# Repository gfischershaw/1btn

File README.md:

# [1btn](http://www.1btn.space)

1btn (one button) uses the internet to complete a task with the simple, satisfying click of a single button. It connects to the internet over Wi-Fi to trigger whatever action you have assigned to it using a simple, online interface. One click, one task. It’s that simple.

Unlike many other “Internet of Things” devices, 1btn does not maintain a continuous connection to the internet. Instead, it sleeps until it is pressed, then it connects to the internet, performs the assigned task, tells you the outcome via its multi-colored LEDs, and then returns to rest.

As the Internet of Things has expanded, we’ve noticed an unfortunate trend: the increasing use of smartphones to control IoT applications. We don’t think a smartphone provides the best or simplest UI for this purpose. Think of all the steps you need to take to send a single instruction with a smartphone: find the phone, wake it up or power it up, enter your passcode, keep swiping until you find and start up your smart app, select the appropriate control, activate it, and then put the phone back to sleep.

We think there’s a better way, a tried-and-true, more intuitive way, to activate a single task or function, and that’s with a button. Why are buttons such a great idea? A button is the simplest user interface for a single-repetitive-programmable task. They are simple exactly because they are designed for a single-task. More importantly, buttons are easy-to-understand, they are familiar, intuitive, and provide immediate, satisfying physical feedback when pushed.

**Specifications**
- Size: about 60mm diameter
- Casing: hexagonal 3D printed using PLA material
- Built-in rechargeable battery: 3.7V 500mAH
- Built-in wifi module: ESP8266 - ESP-12F
- Weight: approx. 50 grams
- Color: white case bottom with multiple color options for the top (red, pink, blue, yellow, white, and green)

## License
See the [LICENSE] (https://github.com/anandtamboli/1btn/blob/master/LICENSE) file

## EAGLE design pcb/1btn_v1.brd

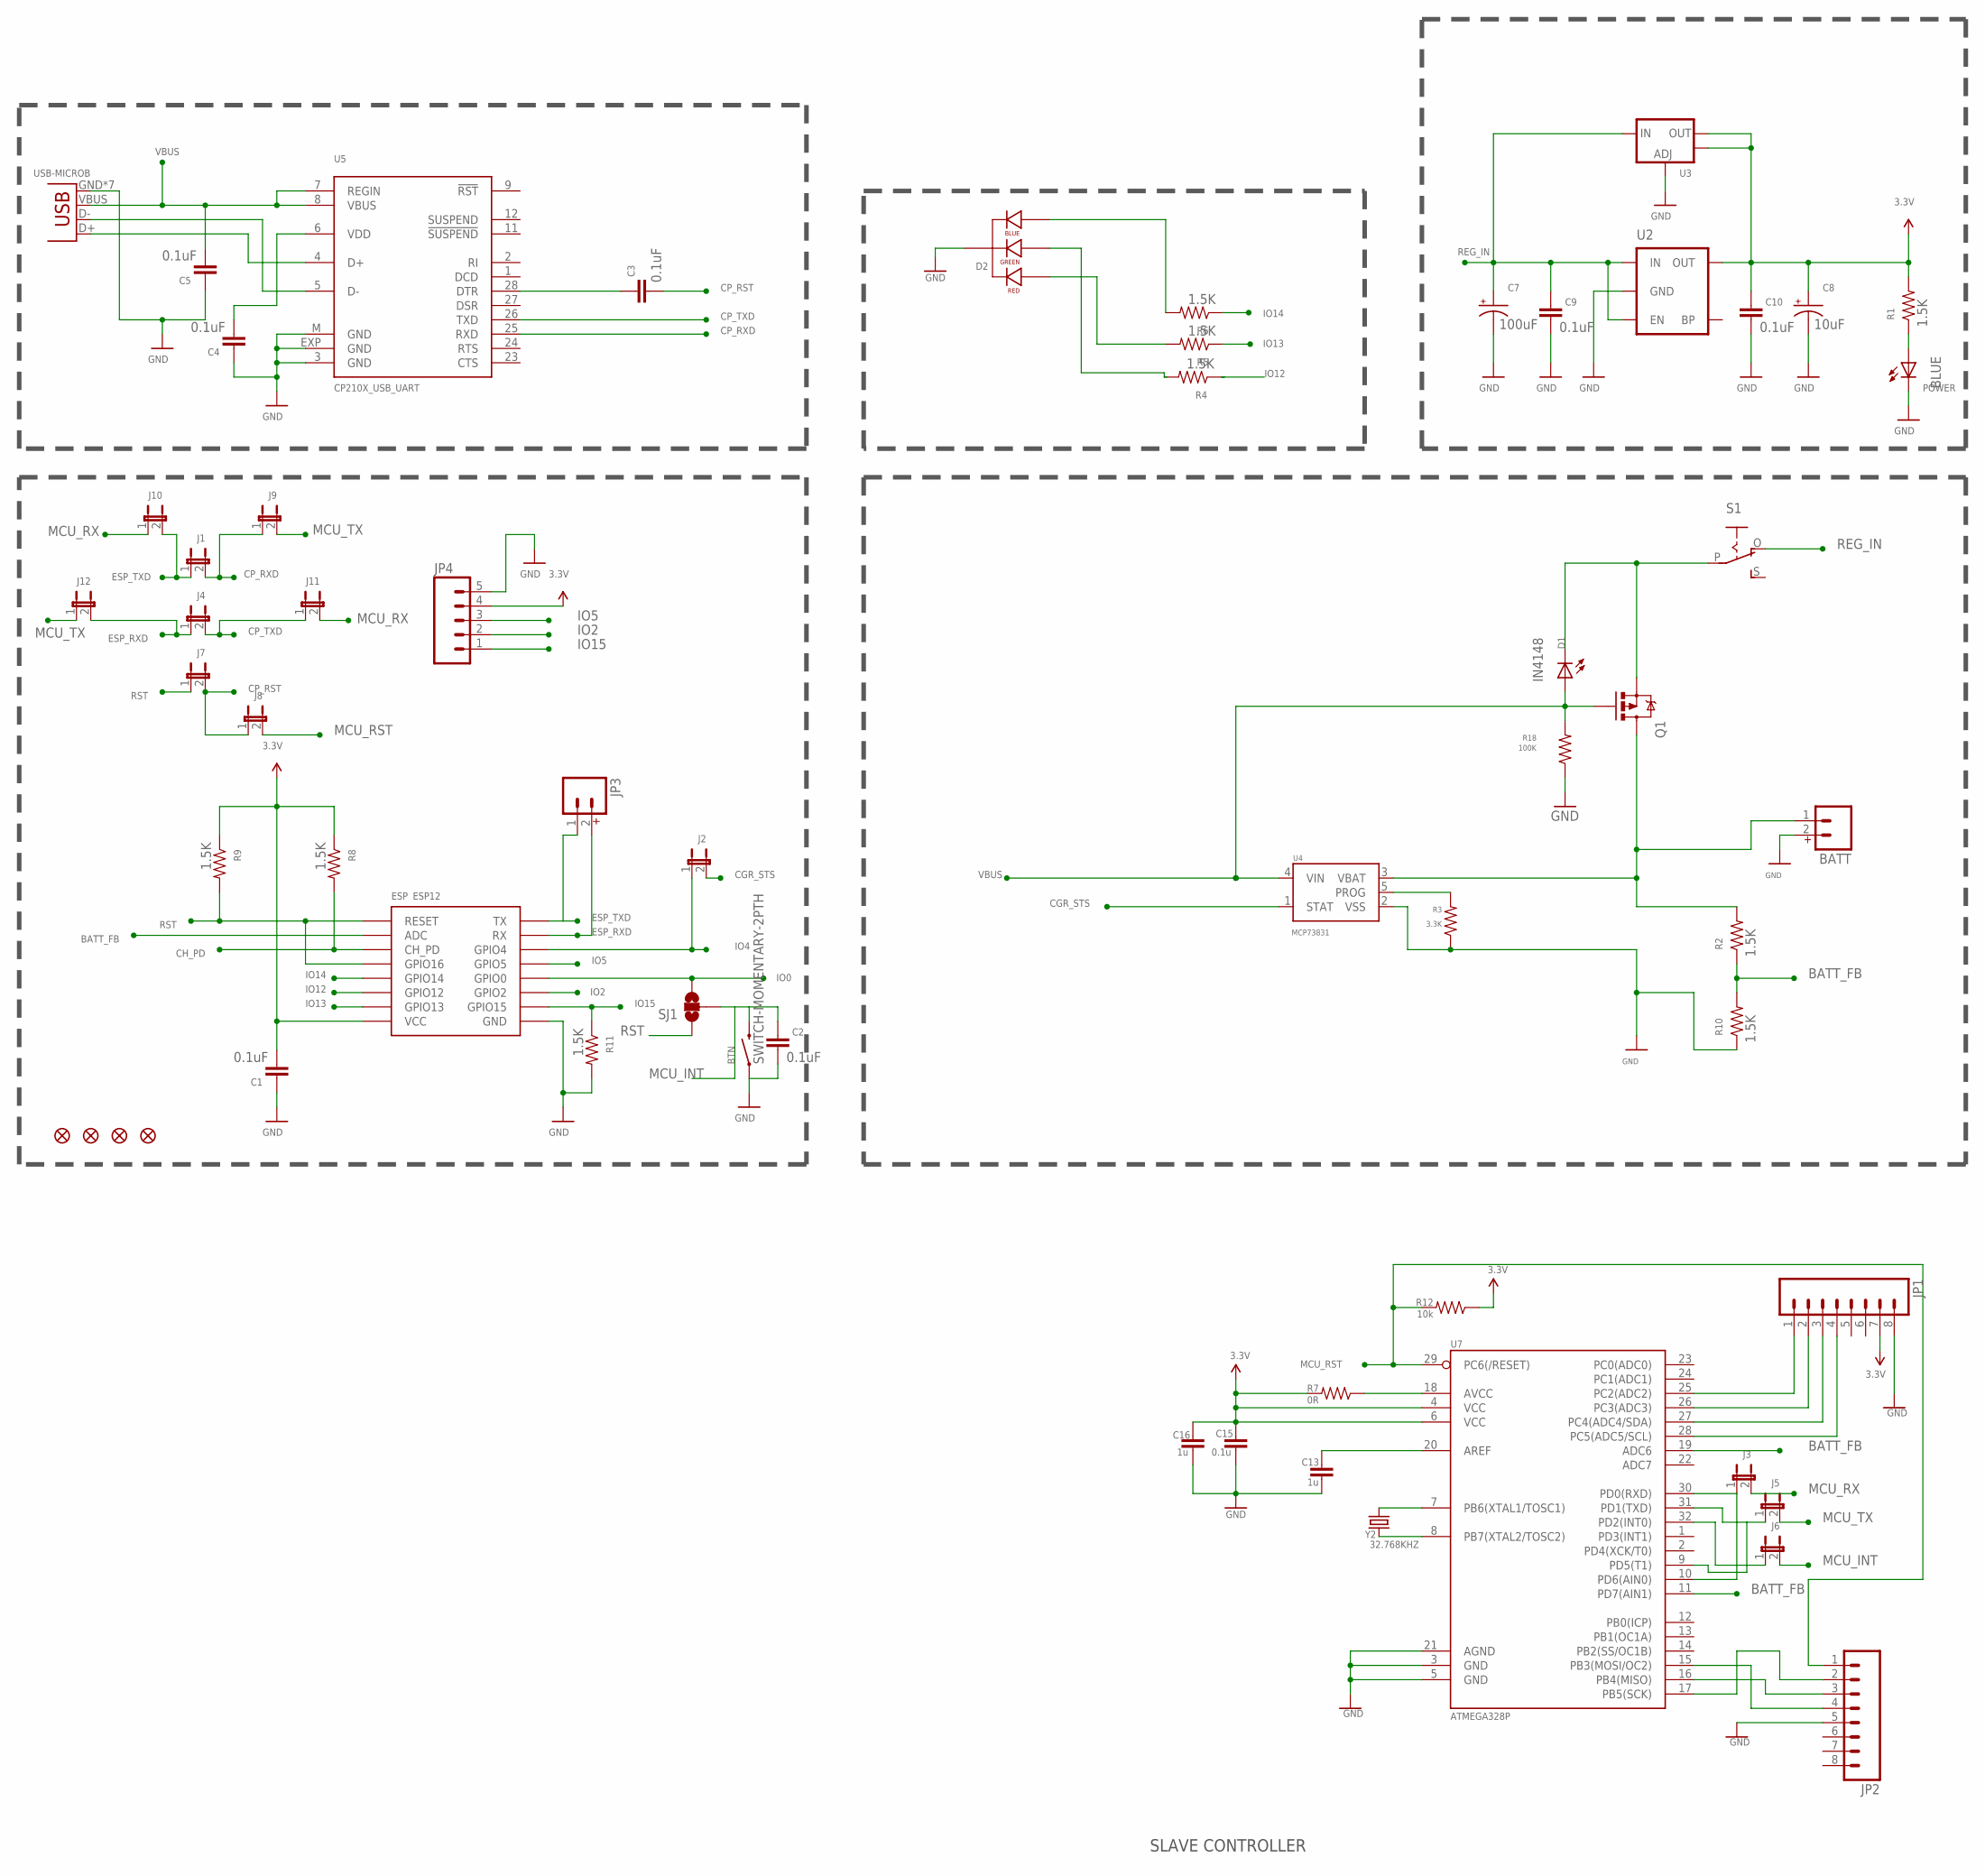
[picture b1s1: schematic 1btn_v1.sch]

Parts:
BATT: M02JST-PTH-2; JST-2-PTH
BTN: SWITCH-MOMENTARY-2PTH; TACTILE-PTH
C1, C2, C3, C4, C5, C9, C10: 0.1uF; 0805
C7: 100uF; EIA3216-KIT
C8: 10uF; EIA3216-KIT
C13, C16: 1u; 0805
C15: 0.1u; 0805
D1: IN4148; LED-1206
D2: LED-RGB-CC-THRUCLEAR; LED-RGB-THRU
ESP: ESP12
FID1, FID2, FID3, FID4: FIDUCIAL1X2; FIDUCIAL-1X2
J1, J2, J3, J4, J5, J6, J7, J8, J9, J10, J11, J12: JUMPER-2SMD-NC; SJ_2S
JP1, JP2: M08NO_SILK; 1X08_PIN1_NO_SILK
JP3: M02PTH; 1X02
JP4: M05PTH; 1X05
POWER: BLUE; LED-0805
Q1: MOSFET-PCHANNELSMD; SOT23-3
R1, R2, R4, R5, R6, R8, R9, R10, R11: 1.5K; 0805
R3: 3.3K; 0805
R7: 0R; 0805
R12: 10k; 0805
R18: 100K; 0805
S1: EG1218S; EG1218
SJ1: SOLDERJUMPER_2WAYS; SJ_3
U2: MIC52053.3V; SOT23-5
U3: V_REG_LM1117SOT223; SOT223
U4: MCP73831; SOT23-5
U5: CP210X_USB_UART; MLP28
U7: ATMEGA328P; TQFP32-08
USB: USB-MICROB
Y2: 32.768KHZ; TC26HEZ

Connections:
3.3V: C1.2, C8.A (+), C10.1, C15.1, C16.1, ESP.VCC, JP1.7, JP4.4, R1.2, R7.2, R8.1, R9.1, R12.1, U2.5 (OUT), U3.2 (OUT), U3.4 (OUT), U7.4 (VCC), U7.6 (VCC)
BA: D2.3 (GREEN_CATHODE), R4.2
BATT+: BATT.1, Q1.3 (D), R2.2, U4.3 (VBAT)
BATT_FB: ESP.ADC, R2.1, R10.2, U7.11 (PD7(AIN1)), U7.19 (ADC6)
CGR_STS: J2.2, U4.1 (STAT)
CH_PD: ESP.CH_PD, R8.2
CP_RST: C3.2, J7.2, J8.1
CP_RXD: J1.2, J9.1, U5.25 (RXD)
CP_TXD: J4.2, J11.1, U5.26 (TXD)
ESP_RXD: ESP.RX, J4.1, J12.2, JP3.2
ESP_TXD: ESP.TX, J1.1, J10.2, JP3.1
GND: BATT.2, BTN.1, C1.1, C2.2, C4.1, C5.1, C7.C (-), C8.C (-), C9.2, C10.2, C13.2, C15.2, C16.2, D2.2 (CATHODE), ESP.GND, JP1.8, JP2.5, JP4.5, POWER.2 (C), R3.1, R10.1, R11.2, R18.1, U2.2 (GND), U3.1 (ADJ), U4.2 (VSS), U5.3 (GND), U5.EXP (GND), U5.M (GND), U7.3 (GND), U7.5 (GND), U7.21 (AGND), USB.GND, USB.MT1 (GND), USB.MT2 (GND), USB.MT3 (GND), USB.MT4 (GND), USB.P$1 (GND), USB.P$2 (GND)
IO0: ESP.GPIO0, SJ1.3
IO2: ESP.GPIO2, JP4.2
IO4: ESP.GPIO4, J2.1
IO5: ESP.GPIO5, JP4.3
IO12: ESP.GPIO12, R4.1
IO13: ESP.GPIO13, R5.1
IO14: ESP.GPIO14, R6.1
IO15: ESP.GPIO15, JP4.1, R11.1
MCU_INT: BTN.3 (2), C2.1, J6.2, SJ1.2
MCU_RST: J8.2, JP2.1, R12.2, U7.29 (PC6(/RESET))
MCU_RX: J3.2, J10.1, J11.2
MCU_TX: J5.2, J9.2, J12.1
unnamed: D2.1 (RED_CATHODE), R5.2
unnamed: D2.4 (BLUE_CATHODE), R6.2
unnamed: D1.C, Q1.2 (S), S1.P
unnamed: U5.5 (D-), USB.D-
unnamed: C3.1, U5.28 (DTR)
unnamed: POWER.1 (A), R1.1
unnamed: U5.4 (D+), USB.D+
unnamed: JP1.1, U7.25 (PC2(ADC2))
unnamed: JP1.2, U7.26 (PC3(ADC3))
unnamed: JP1.3, U7.27 (PC4(ADC4/SDA))
unnamed: JP1.4, U7.28 (PC5(ADC5/SCL))
unnamed: R3.2, U4.5 (PROG)
unnamed: JP2.4, U7.15 (PB3(MOSI/OC2))
unnamed: JP2.3, U7.16 (PB4(MISO))
unnamed: JP2.2, U7.17 (PB5(SCK))
unnamed: J3.1, U7.10 (PD6(AIN0)), U7.30 (PD0(RXD))
unnamed: J6.1, U7.32 (PD2(INT0))
unnamed: J5.1, U7.9 (PD5(T1)), U7.31 (PD1(TXD))
unnamed: U7.7 (PB6(XTAL1/TOSC1)), Y2.2
unnamed: U7.8 (PB7(XTAL2/TOSC2)), Y2.1
unnamed: C13.1, U7.20 (AREF)
unnamed: R7.1, U7.18 (AVCC)
REG_IN: C7.A (+), C9.1, S1.O, U2.1 (IN), U2.3 (EN), U3.3 (IN)
RST: ESP.GPIO16, ESP.RESET, J7.1, R9.2, SJ1.1
VBUS: C5.2, D1.A, Q1.1 (G), R18.2, U4.4 (VIN), U5.7 (REGIN), U5.8 (VBUS), USB.VBUS
VDD: C4.2, U5.6 (VDD)

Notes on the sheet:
SLAVE CONTROLLER

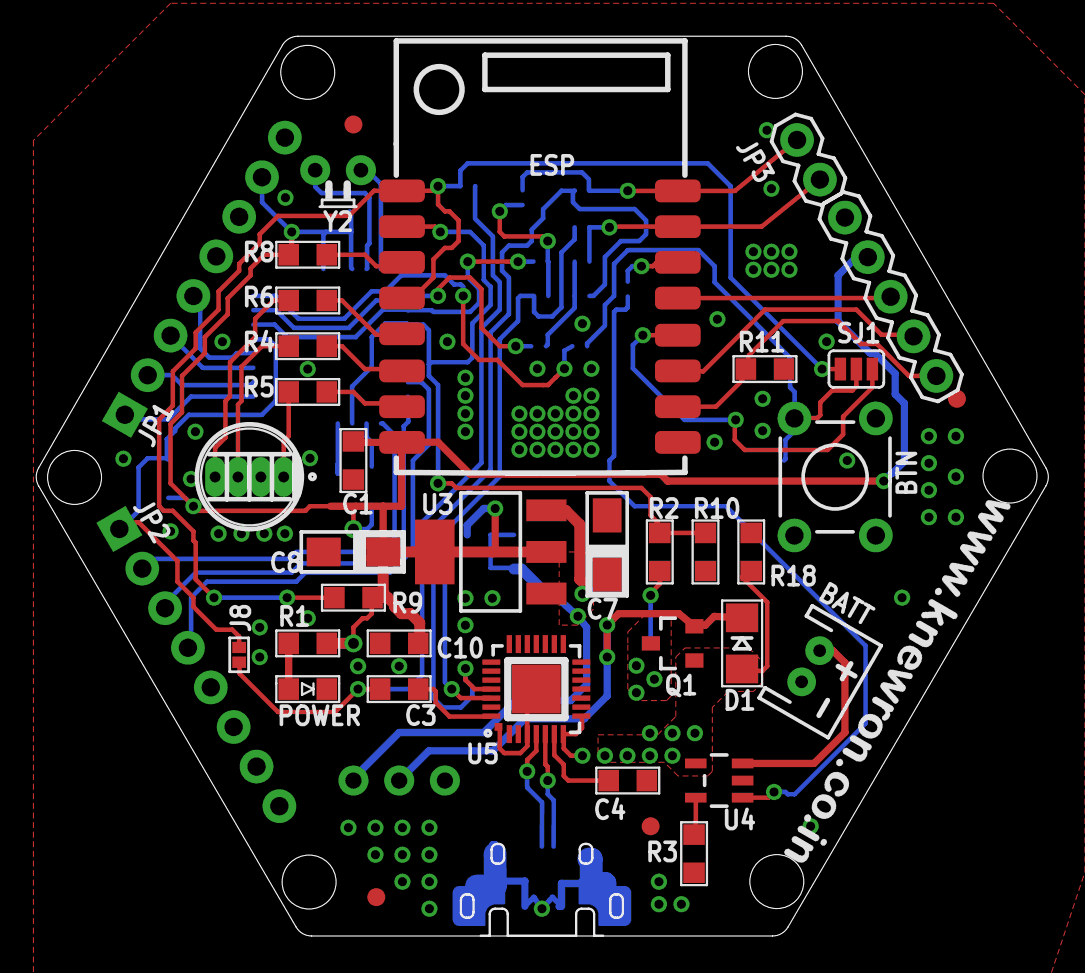
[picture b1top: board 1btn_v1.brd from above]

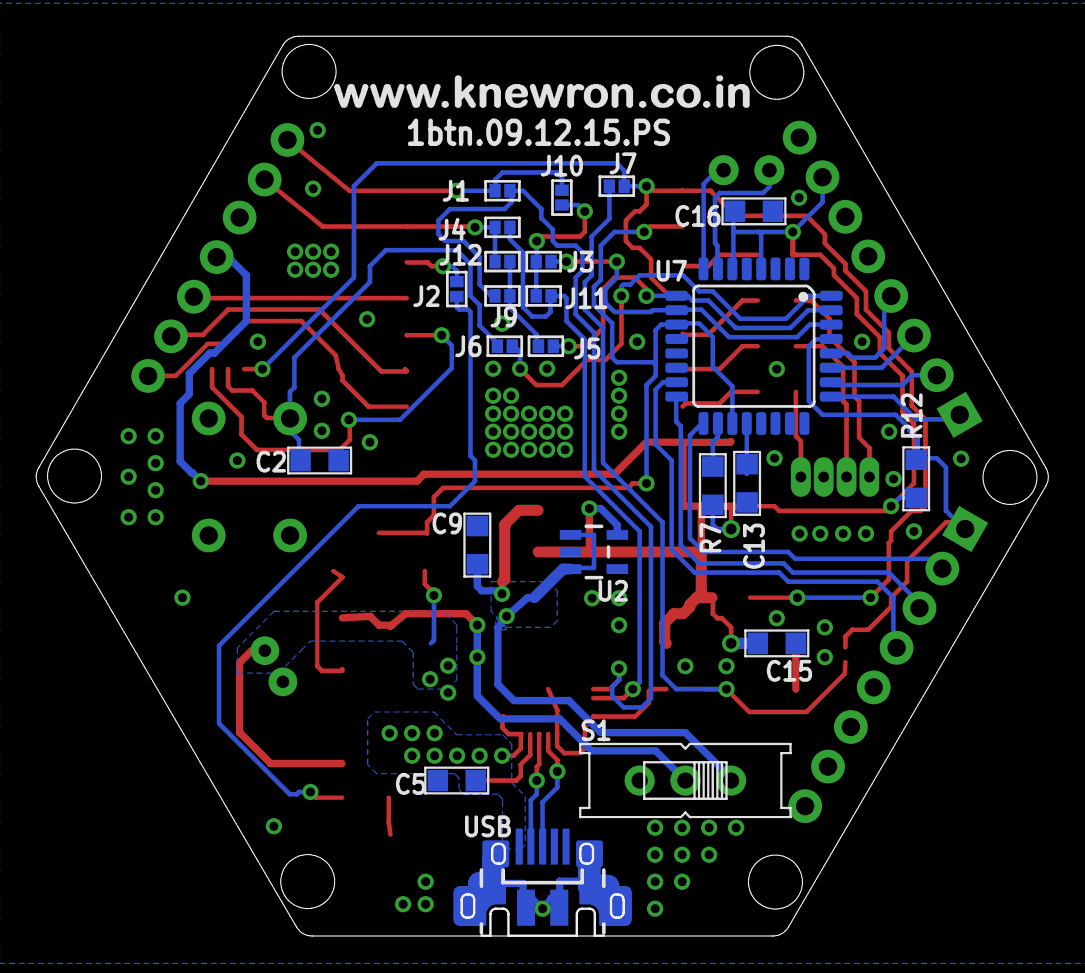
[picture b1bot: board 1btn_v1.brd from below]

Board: 2 copper layers, 56.1 x 49.9 mm, 63 parts (24 on the bottom side), 50 nets.

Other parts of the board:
U$2, U$3: WEBLINK-2

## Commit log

2016-03-18 GIT Initialized
2016-03-18 1btn images added
2016-03-18 images added
2016-03-18 Files updated
2016-03-18 New readme file updated
2016-03-18 Licensing changed
2016-03-18 New information added
2016-03-18 Firmware files added
2016-03-18 Folder re-org
2016-03-18 Added mechanical designs
2016-03-18 PCB files added
2016-03-18 Battery test results added
2016-03-18 Battery test results updated
2016-03-18 Create gh-pages branch via GitHub
2016-03-27 comparison image added
2016-03-27 hack # 1 added
2016-03-27 directory restructuring
2016-03-27 use case 1 added
2016-03-30 hack # 1 updated
2016-04-04 IFTTT timelogger use case added
2016-04-23 BOM and use case files updated
2016-05-11 schematic file added in image format
2016-05-11 layout images added
2016-06-07 production update - images and writeup added
2016-06-28 firmware updated
2016-06-28 user manual added
2016-07-08 production update 8 July 16
2016-08-15 firmware v3 with configuration bug resolved
2016-09-15 The remaining files
2016-09-15 Described easier method of entering program mode
2016-09-16 assert loadfile() not loadfile.

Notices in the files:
parts and their libraries:
SparkFun-Electromechanical: Licensing: CC v3.0 Share-Alike You are welcome to use this library for commercial purposes.
SparkFun-Connectors: Licensing: Creative Commons ShareAlike 4.0 International - https://creativecommons.org/licenses/by-sa/4.0
Knewron: (c) 2012
